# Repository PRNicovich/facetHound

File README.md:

# Facet Hound

Open hardware and software for the Facet Hound digital lapidary faceting machine.

Facet Hound is a mast-style faceting machine with digital readouts on all three axes, electronic indexing precise to less than 0.01 degrees, and a direct-driven lap powered by a brushless DC motor. It is designed to be replicated with readily available components and a minimum of custom parts. In 2025, the included components cost approximately $1,600.

Complete v7 and v8 assemblies are included as `Hardware/FacetHoundv7.step` and `Hardware/FacetHoundv8.step`. Subfolders of `Hardware/` contain vendor files for machining (`.step`, `.pdf`), 3D printing (`.stl`), PCB fabrication (`.brd`), and laser/plasma/waterjet cutting (`.dxf`). Commercially available parts are identified in the main design.

Subfolders of `Software/` contain the Arduino C++ sketches and desktop Python tools. The main module is a Raspberry Pi Pico 2, while peripheral controllers use RP2040 Zero boards.

## Current firmware

The current Pico 2 base plus RP2040 Zero mast, display, and keyboard-host
release is in
[`Software/FacetHound_SD_Loader`](Software/FacetHound_SD_Loader). It includes:

- Classic, Dynamic, and Static HX8357D display modes.
- A twist-wheel settings UI for machine and display configuration.
- Persistent CW/CCW indexing, Table Adapter, servo, calibration, and axis settings.
- Variable-length mark points with direct numeric editing.
- GemCad `.asc` and Facet Hound `.fct` loading from microSD.
- Source-validated `.fhc` geometry caching and a PC bulk converter.
- Runtime convex-gem mesh generation on the Pico 2 and streaming to the display.
- A documented USB CDC API and PC diagnostic/motion-test console.
- Matching streaming mast telemetry for tip, index, and force sensing.
- A dedicated PIO-USB keyboard host with the matching UART key protocol.

See the [release README](Software/FacetHound_SD_Loader/README.md) for SD wiring, dependencies, flashing instructions, limits, and verification results.

## Repository map

- `Hardware/`: complete assemblies and fabrication files.
- `Software/FacetHound_SD_Loader/`: current four-controller firmware release.
- `Software/caseModule/` and `displayModule/`: earlier module sketches.
- `Software/gemUtils/`: GemCad parsing, display prototypes, and geometry utilities.
- `Software/engraveUtils/`: engraving experiments.

These designs remain preliminary and may contain incomplete or untested elements. Contributions and bug fixes are welcome as pull requests.

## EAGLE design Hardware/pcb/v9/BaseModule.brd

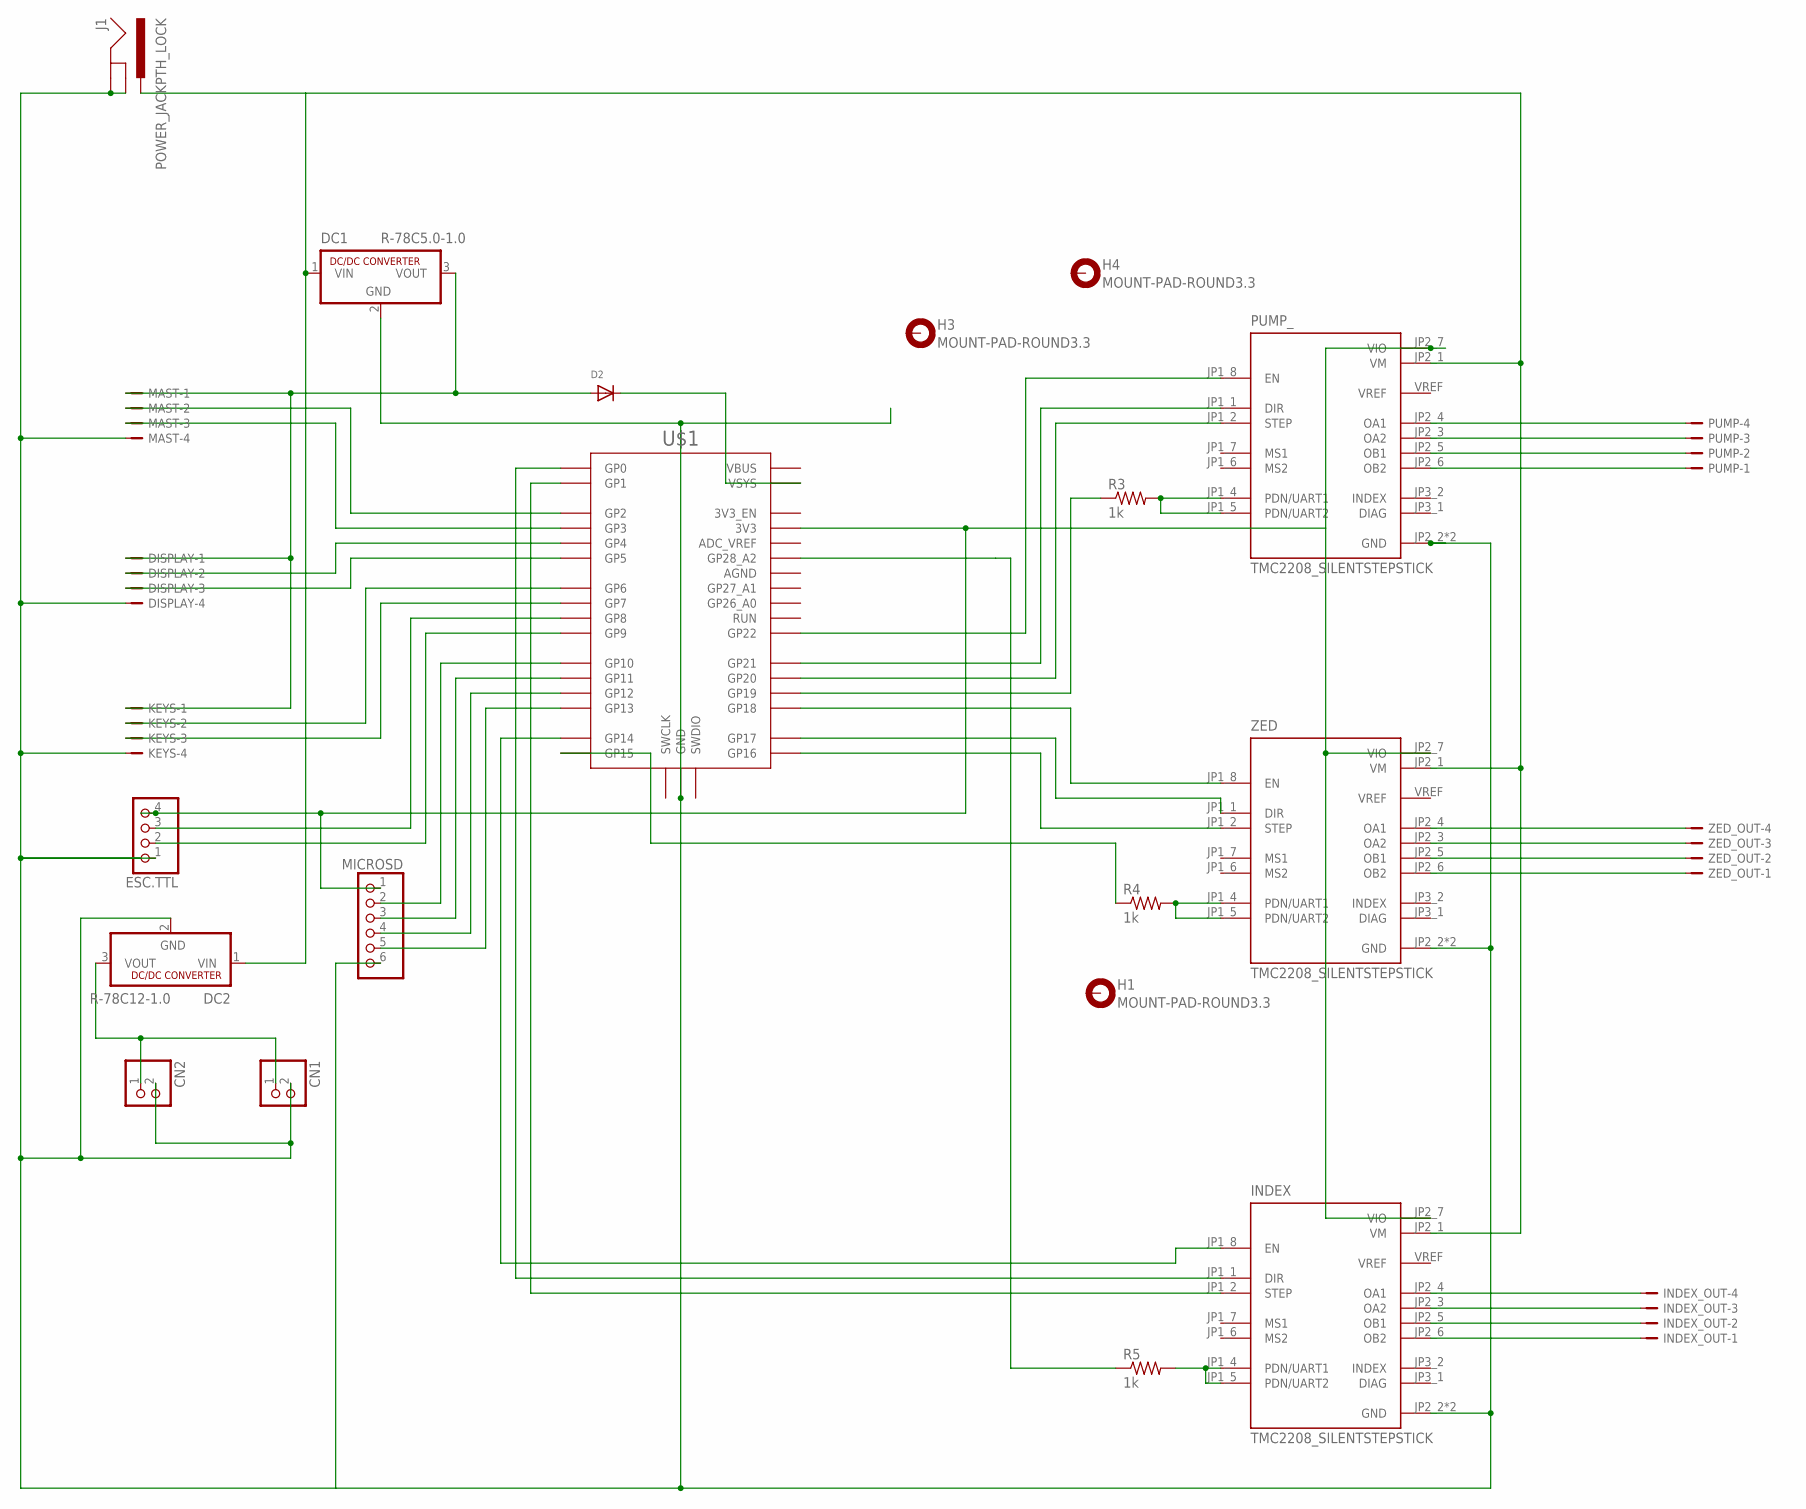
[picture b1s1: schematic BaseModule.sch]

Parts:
CN1, CN2: JST_2PIN-THM-RA; JST-PH-2-THM-RA
D2: DIODESMA; SMADIODE
DC1: R-78C5.0-1.0; SIP3
DC2: R-78C12-1.0; SIP3
DISPLAY: JST-PH-4_TH-V; B4B-PH-K-S
ESC.TTL: PINHD-1X4; 1X04
H1, H3, H4: MOUNT-PAD-ROUND3.3; 3,3-PAD
INDEX: TMC2208_SILENTSTEPSTICK; MODULE_TMC2208_SILENTSTEPSTICK
INDEX_OUT: JST-PH-4_TH-RA; S4B-PH-KL
J1: POWER_JACKPTH_LOCK; POWER_JACK_PTH_LOCK
KEYS: JST-PH-4_TH-V; B4B-PH-K-S
MAST: JST-PH-4_TH-V; B4B-PH-K-S
MICROSD: PINHD-1X6; 1X06
PUMP: JST-PH-4_TH-RA; S4B-PH-KL
PUMP_: TMC2208_SILENTSTEPSTICK; MODULE_TMC2208_SILENTSTEPSTICK
R3, R4, R5: 1k; R1206
U$1: RPI_PICO-TH; RPI_PICO_TH
ZED: TMC2208_SILENTSTEPSTICK; MODULE_TMC2208_SILENTSTEPSTICK
ZED_OUT: JST-PH-4_TH-RA; S4B-PH-KL

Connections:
5V: D2.C, U$1.VSYS
GND: CN1.2 (1), CN2.2 (1), DC1.2 (GND), DC2.2 (GND), DISPLAY.4, ESC.TTL.1, INDEX.JP2_2 (GND), INDEX.JP2_8 (GND), J1.GND, J1.GNDBREAK, KEYS.4, MAST.4, MICROSD.6, PUMP_.JP2_2 (GND), PUMP_.JP2_8 (GND), U$1.GND@1 (GND), U$1.GND@2 (GND), U$1.GND@3 (GND), U$1.GND@4 (GND), U$1.GND@5 (GND), U$1.GND@6 (GND), U$1.GND@7 (GND), U$1.GND@8 (GND), ZED.JP2_2 (GND), ZED.JP2_8 (GND)
KEYS: KEYS.2, U$1.GP6
unnamed: MICROSD.2, U$1.GP10
unnamed: MICROSD.3, U$1.GP11
unnamed: PUMP_.JP1_4 (PDN/UART1), PUMP_.JP1_5 (PDN/UART2), R3.2
unnamed: R4.2, ZED.JP1_4 (PDN/UART1), ZED.JP1_5 (PDN/UART2)
unnamed: DC1.1 (VIN), DC2.1 (VIN), INDEX.JP2_1 (VM), J1.PWR, PUMP_.JP2_1 (VM), ZED.JP2_1 (VM)
unnamed: U$1.GP18, ZED.JP1_8 (EN)
unnamed: INDEX.JP2_4 (OA1), INDEX_OUT.4
unnamed: MICROSD.4, U$1.GP12
unnamed: ESC.TTL.4, INDEX.JP2_7 (VIO), MICROSD.1, PUMP_.JP2_7 (VIO), U$1.3V3, ZED.JP2_7 (VIO)
unnamed: MICROSD.5, U$1.GP13
unnamed: R4.1, U$1.GP15
unnamed: D2.A, DC1.3 (VOUT), DISPLAY.1, KEYS.1, MAST.1
unnamed: INDEX.JP2_3 (OA2), INDEX_OUT.3
unnamed: ZED.JP2_4 (OA1), ZED_OUT.4
unnamed: ZED.JP2_3 (OA2), ZED_OUT.3
unnamed: ZED.JP2_5 (OB1), ZED_OUT.2
unnamed: ZED.JP2_6 (OB2), ZED_OUT.1
unnamed: PUMP.4, PUMP_.JP2_4 (OA1)
unnamed: PUMP.3, PUMP_.JP2_3 (OA2)
unnamed: PUMP.2, PUMP_.JP2_5 (OB1)
unnamed: PUMP.1, PUMP_.JP2_6 (OB2)
unnamed: U$1.GP17, ZED.JP1_1 (DIR)
unnamed: U$1.GP16, ZED.JP1_2 (STEP)
unnamed: PUMP_.JP1_8 (EN), U$1.GP22
unnamed: PUMP_.JP1_1 (DIR), U$1.GP21
unnamed: PUMP_.JP1_2 (STEP), U$1.GP20
unnamed: R3.1, U$1.GP19
unnamed: MAST.2, U$1.GP2
unnamed: MAST.3, U$1.GP3
unnamed: DISPLAY.2, U$1.GP4
unnamed: DISPLAY.3, U$1.GP5
unnamed: KEYS.3, U$1.GP7
unnamed: ESC.TTL.3, U$1.GP8
unnamed: INDEX.JP2_5 (OB1), INDEX_OUT.2
unnamed: ESC.TTL.2, U$1.GP9
unnamed: CN1.1 (2), CN2.1 (2), DC2.3 (VOUT)
unnamed: INDEX.JP2_6 (OB2), INDEX_OUT.1
unnamed: INDEX.JP1_8 (EN), U$1.GP14
unnamed: R5.1, U$1.GP28_A2
unnamed: INDEX.JP1_4 (PDN/UART1), INDEX.JP1_5 (PDN/UART2), R5.2
unnamed: INDEX.JP1_1 (DIR), U$1.GP0
unnamed: INDEX.JP1_2 (STEP), U$1.GP1

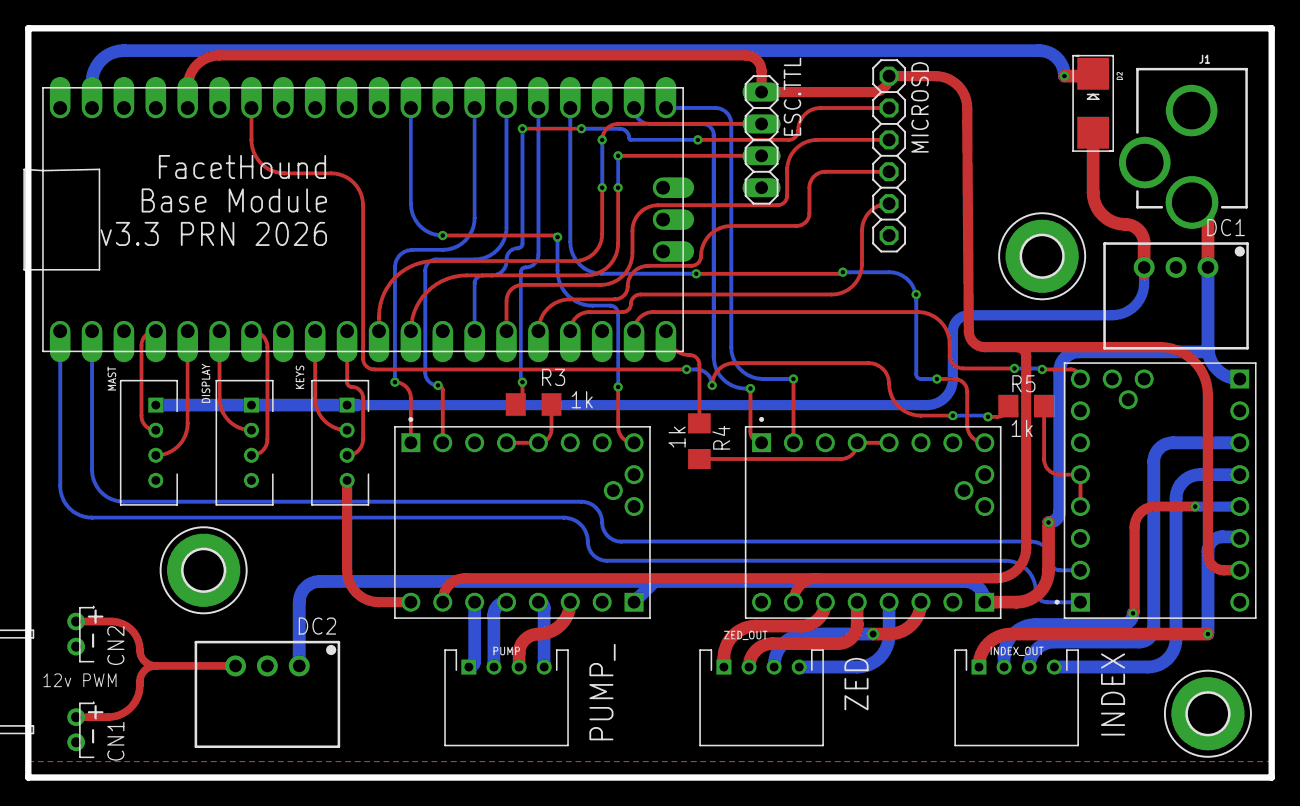
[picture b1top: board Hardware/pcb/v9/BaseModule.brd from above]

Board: 2 copper layers, 99.1 x 59.7 mm, 24 parts (0 on the bottom side), 45 nets.

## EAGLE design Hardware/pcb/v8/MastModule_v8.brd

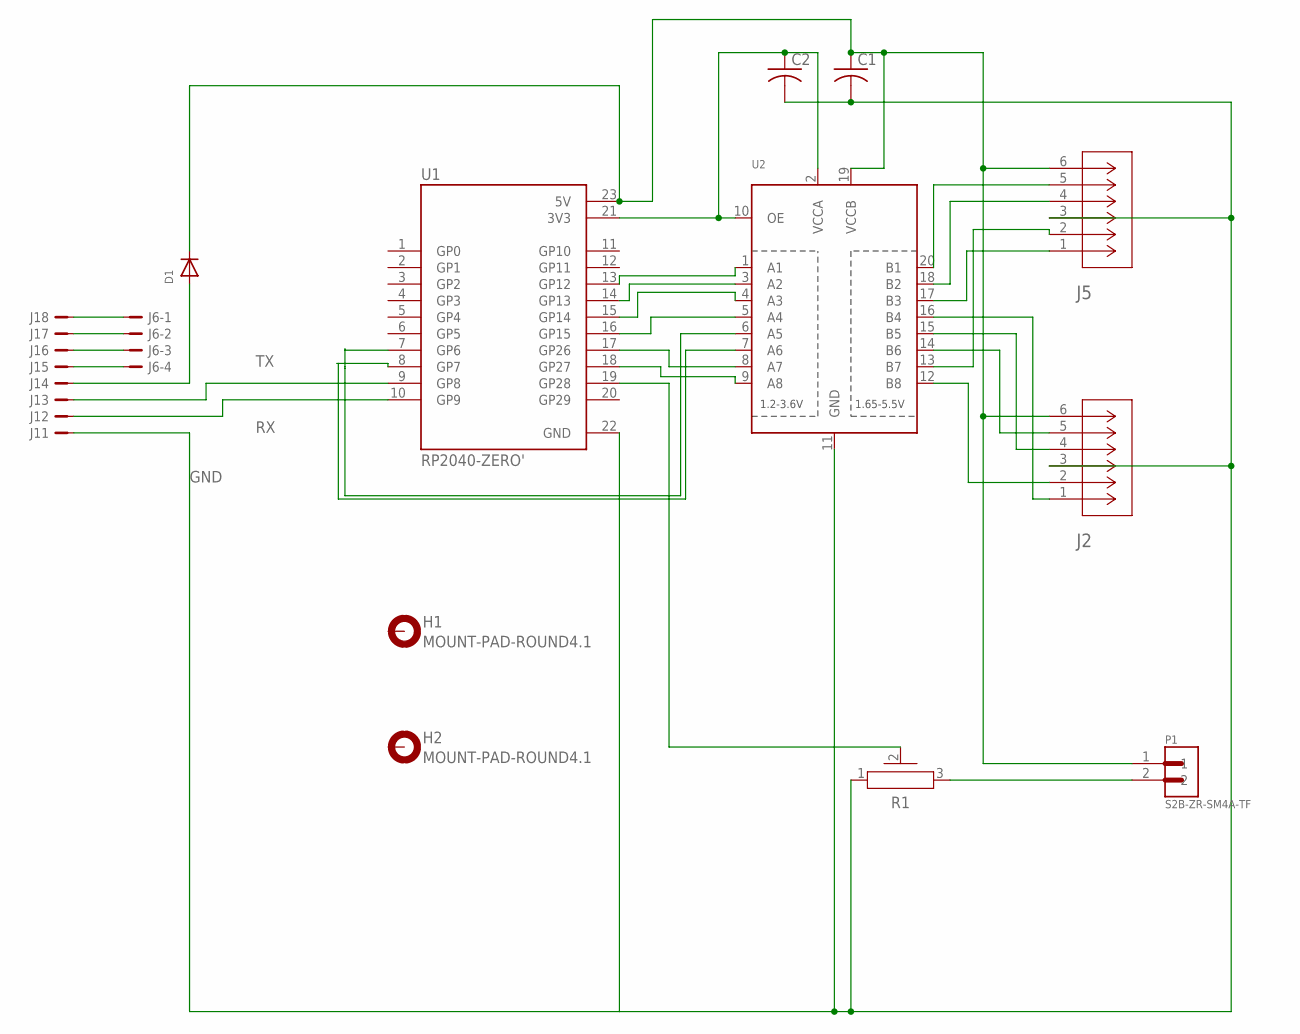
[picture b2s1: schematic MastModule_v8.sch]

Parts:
C1, C2: C-USC1210; C1210
D1: DIODESMA; SMADIODE
H1, H2: MOUNT-PAD-ROUND4.1; 4,1-PAD
J1: B8B-PH-K-S
J2, J5: 2132260630CONN_2132260000-SD_06_MOL; CONN_2132260000-SD_06_MOL
J6: JST-PH-4_TH-RA; S4B-PH-KL
P1: S2B-ZR-SM4A-TF; JST_S2B-ZR-SM4A-TF
R1: PV36X
U1: RP2040-ZERO'; MODULE_RP2040-ZERO
U2: TXB0108PWR; TSSOP20

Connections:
3V3: C2.1, U1.21 (3V3), U2.2 (VCCA), U2.10 (OE)
5V: C1.1, D1.C, J2.6, J5.6, P1.1, U1.23 (5V), U2.19 (VCCB)
GND: C1.2, C2.2, J1.1, J2.3, J5.3, R1.1, U1.22 (GND), U2.11 (GND)
unnamed: J1.8, J6.1
unnamed: J1.7, J6.2
unnamed: J1.6, J6.3
unnamed: J1.5, J6.4
unnamed: D1.A, J1.4
unnamed: U1.17 (GP26), U2.8 (A7)
unnamed: J5.5, U2.20 (B1)
unnamed: J5.4, U2.18 (B2)
unnamed: R1.2, U1.19 (GP28)
unnamed: P1.2, R1.3
unnamed: J5.1, U2.17 (B3)
unnamed: J2.1, U2.16 (B4)
unnamed: J2.4, U2.15 (B5)
unnamed: J2.5, U2.14 (B6)
unnamed: U1.18 (GP27), U2.9 (A8)
unnamed: J5.2, U2.13 (B7)
unnamed: J2.2, U2.12 (B8)
unnamed: U1.8 (GP7), U2.7 (A6)
unnamed: U1.7 (GP6), U2.6 (A5)
unnamed: U1.13 (GP12), U2.1 (A1)
unnamed: U1.14 (GP13), U2.3 (A2)
unnamed: U1.15 (GP14), U2.4 (A3)
unnamed: U1.16 (GP15), U2.5 (A4)
RX: J1.2, U1.10 (GP9)
TX: J1.3, U1.9 (GP8)

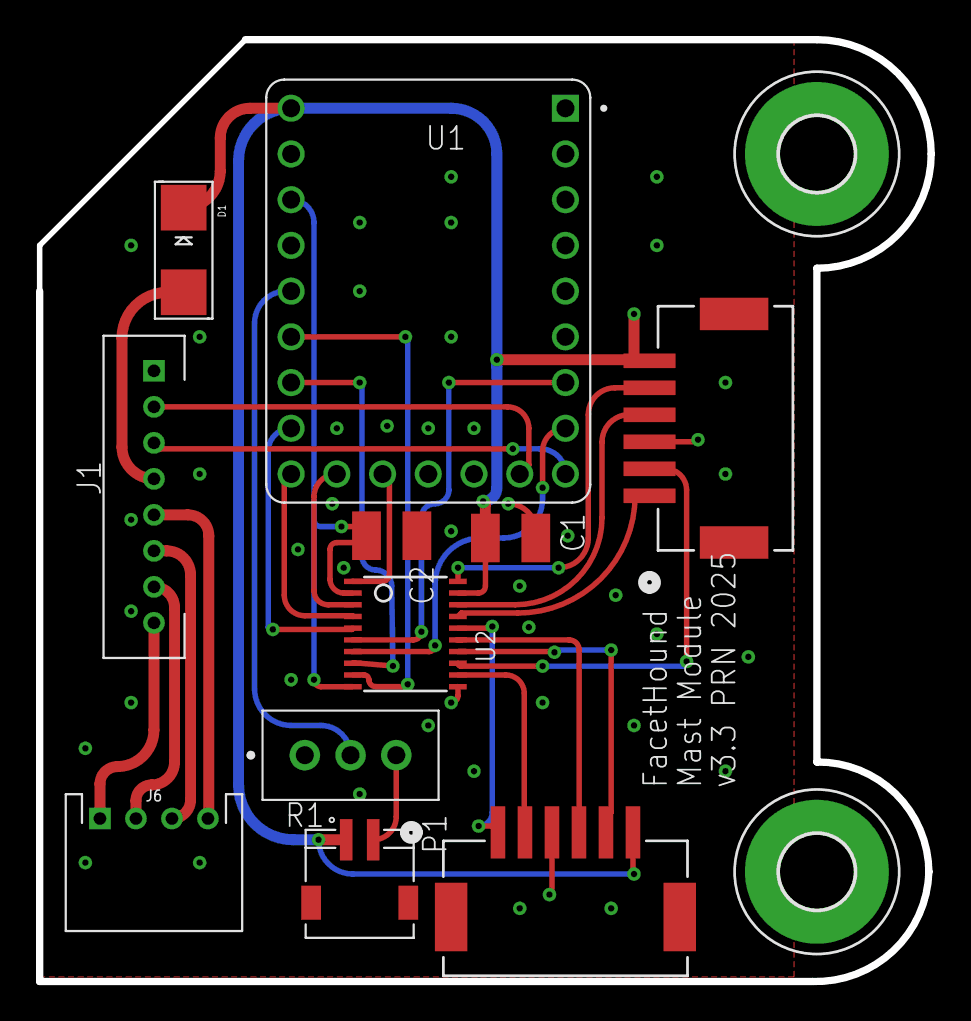
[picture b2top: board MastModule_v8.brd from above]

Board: 2 copper layers, 49.5 x 52.3 mm, 13 parts (0 on the bottom side), 28 nets.

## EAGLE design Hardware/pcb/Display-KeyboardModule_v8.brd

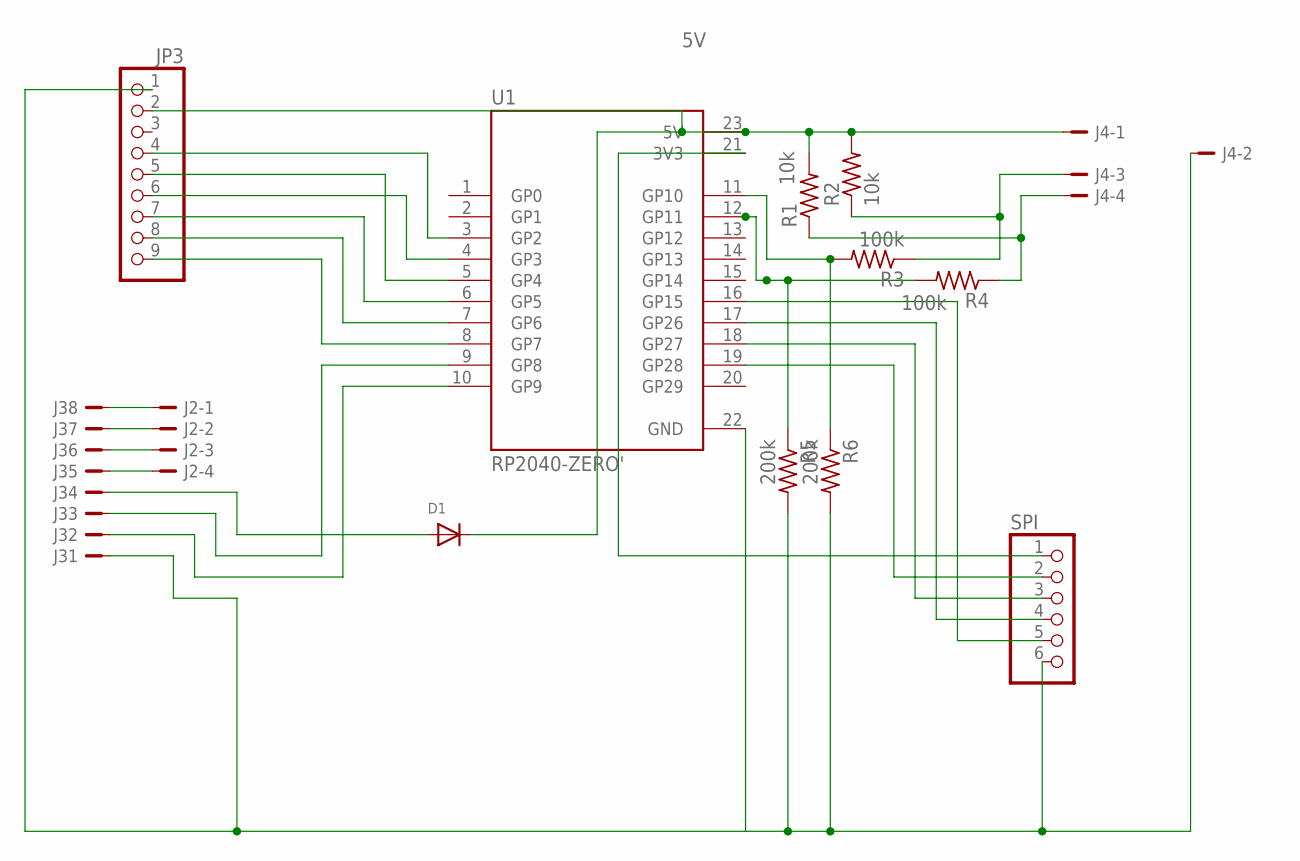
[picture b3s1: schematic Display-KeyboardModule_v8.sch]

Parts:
D1: DIODESMA; SMADIODE
J2, J4: JST-PH-4_TH-RA; S4B-PH-KL
J3: B8B-PH-K-S
JP3: PINHD-1X9; 1X09-BIG
R1, R2: 10k; R1206
R3, R4: 100k; R1206
R5, R6: 200k; R1206
SPI: PINHD-1X6; 1X06
U1: RP2040-ZERO'; MODULE_RP2040-ZERO

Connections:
5V: D1.C, J4.1, JP3.2, R1.2, R2.2, U1.23 (5V)
GND: J3.1, J4.2, JP3.1, R5.2, R6.2, SPI.6, U1.22 (GND)
unnamed: D1.A, J3.4
unnamed: J2.1, J3.8
unnamed: JP3.4, U1.3 (GP2)
unnamed: J3.3, U1.9 (GP8)
unnamed: J3.2, U1.10 (GP9)
unnamed: JP3.6, U1.4 (GP3)
unnamed: JP3.5, U1.5 (GP4)
unnamed: JP3.7, U1.6 (GP5)
unnamed: JP3.8, U1.7 (GP6)
unnamed: JP3.9, U1.8 (GP7)
unnamed: SPI.2, U1.19 (GP28)
unnamed: J4.3, R2.1, R3.1
unnamed: J2.2, J3.7
unnamed: J2.3, J3.6
unnamed: J2.4, J3.5
unnamed: SPI.3, U1.18 (GP27)
unnamed: J4.4, R1.1, R4.1
unnamed: SPI.4, U1.17 (GP26)
unnamed: R3.2, R6.1, U1.11 (GP10)
unnamed: SPI.5, U1.16 (GP15)
unnamed: SPI.1, U1.21 (3V3)
unnamed: R4.2, R5.1, U1.12 (GP11)

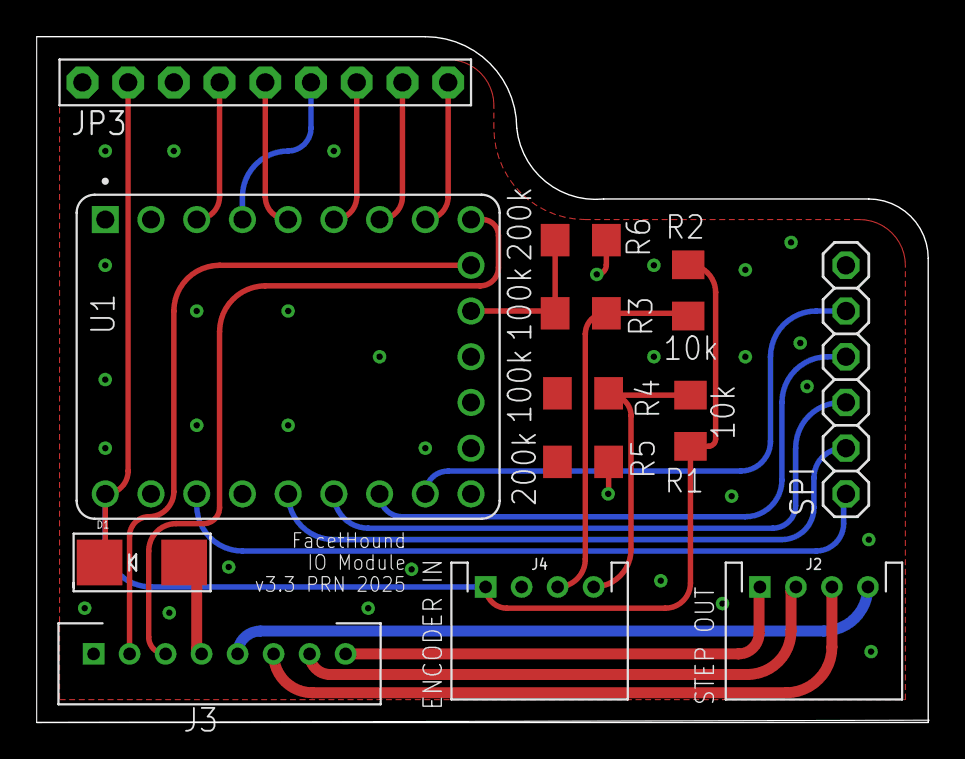
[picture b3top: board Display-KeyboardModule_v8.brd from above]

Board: 2 copper layers, 49.5 x 38.1 mm, 13 parts (0 on the bottom side), 24 nets.

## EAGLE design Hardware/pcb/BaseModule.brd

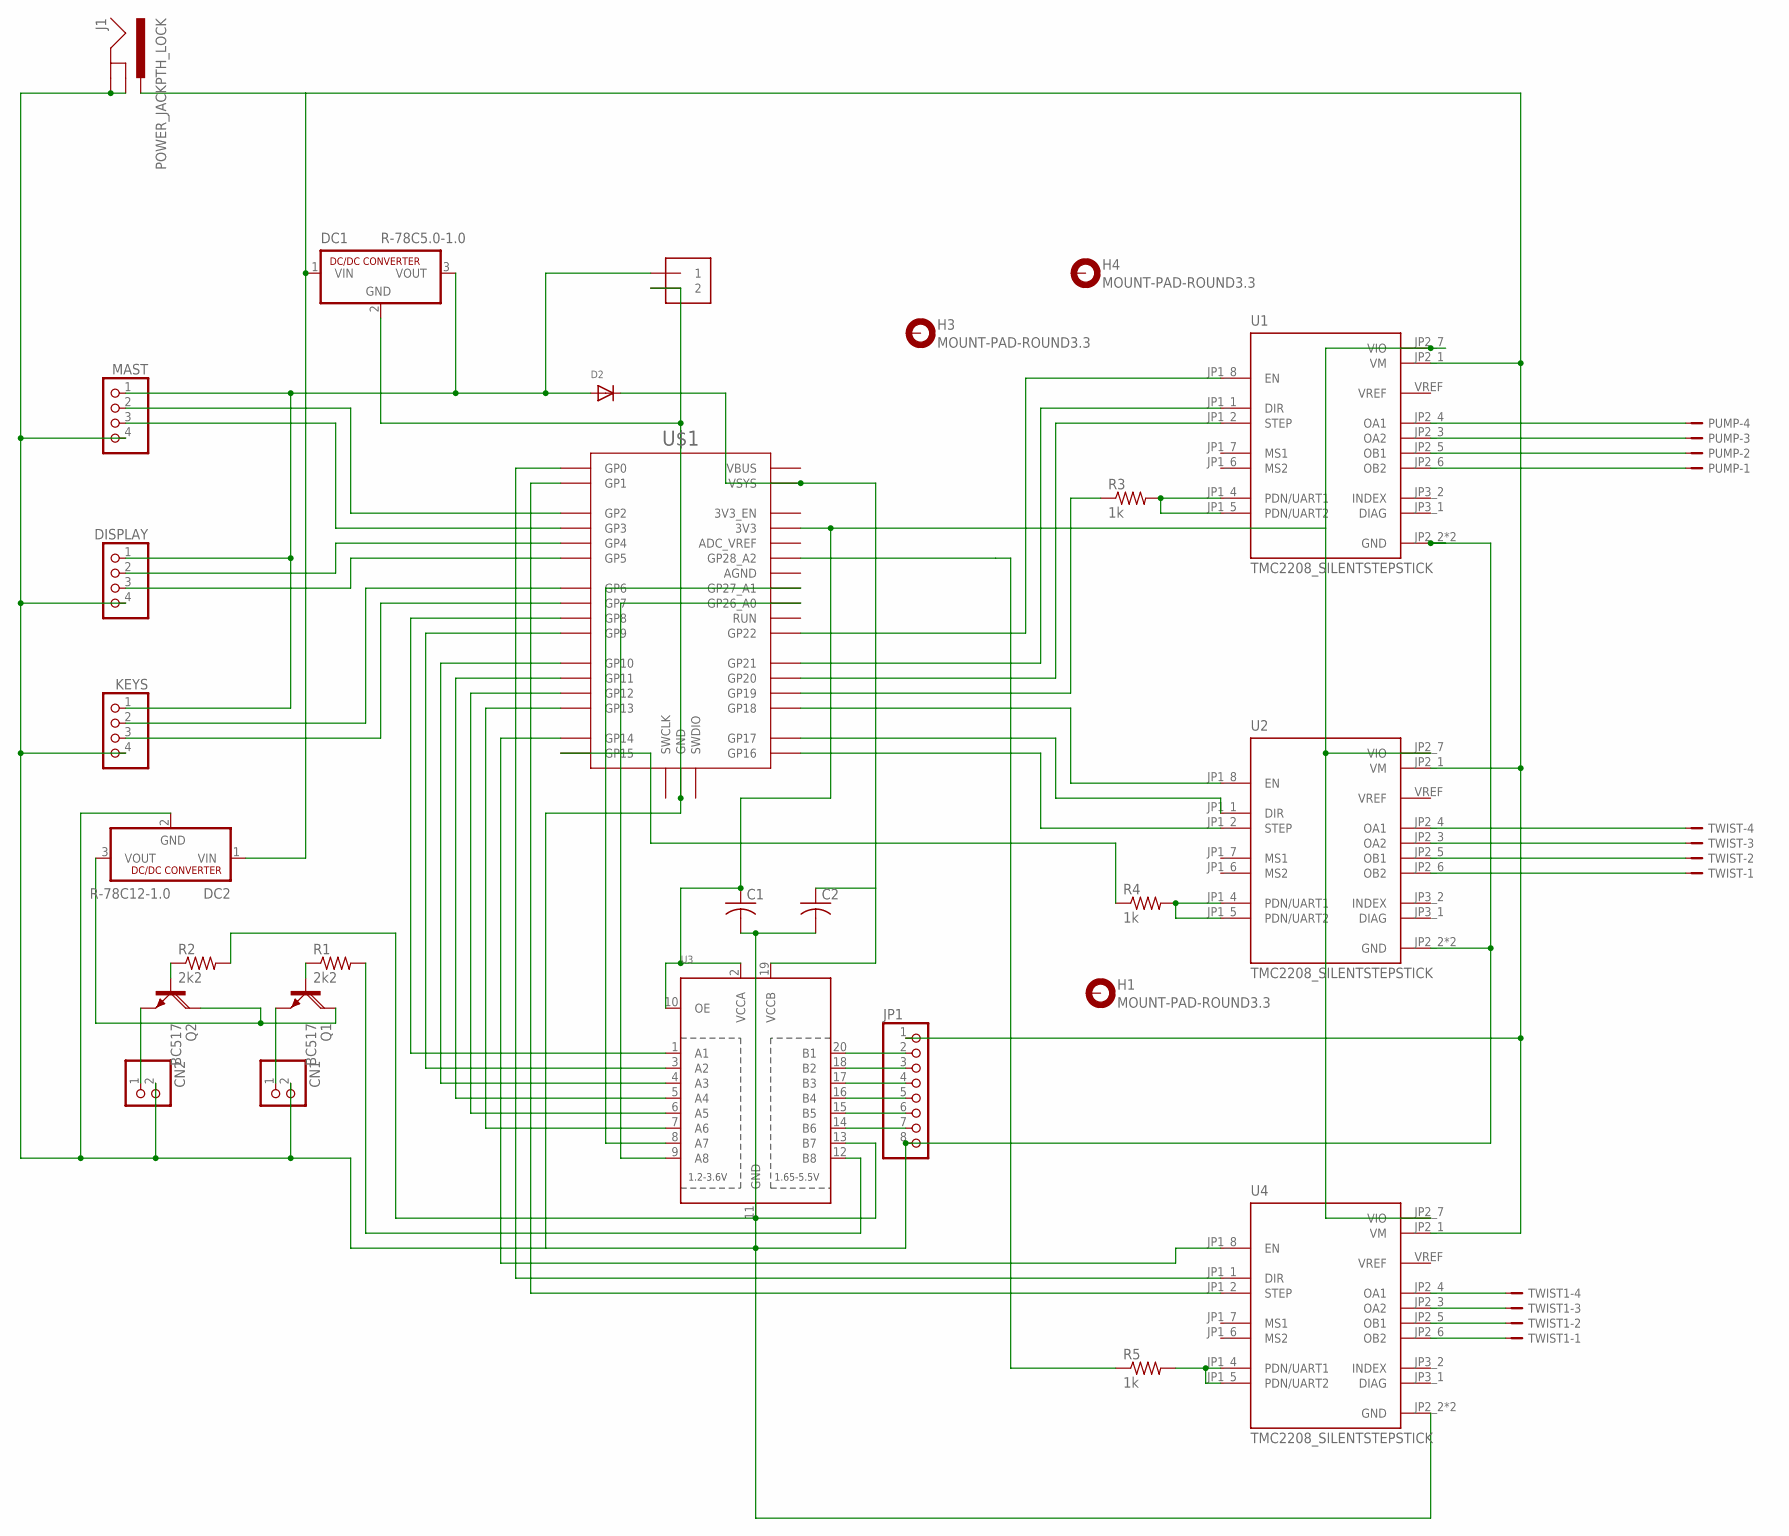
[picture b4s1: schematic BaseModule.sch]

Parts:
C1, C2: C-USC1206; C1206
CN1, CN2: JST_2PIN-THM-RA; JST-PH-2-THM-RA
D2: DIODESMA; SMADIODE
DC1: R-78C5.0-1.0; SIP3
DC2: R-78C12-1.0; SIP3
DISPLAY: PINHD-1X4; 1X04
H1, H3, H4: MOUNT-PAD-ROUND3.3; 3,3-PAD
J1: POWER_JACKPTH_LOCK; POWER_JACK_PTH_LOCK
J2: 1X2-3.5MM
JP1: PINHD-1X8-3.5MM; 1X08-3.5MM
KEYS: PINHD-1X4; 1X04
MAST: PINHD-1X4; 1X04
PUMP: JST-PH-4_TH-RA; S4B-PH-KL
Q1, Q2: BC517; SOT54A
R1, R2: 2k2; R1206
R3, R4, R5: 1k; R1206
TWIST, TWIST1: JST-PH-4_TH-RA; S4B-PH-KL
U1, U2, U4: TMC2208_SILENTSTEPSTICK; MODULE_TMC2208_SILENTSTEPSTICK
U3: TXB0108PWR; TSSOP20
U$1: RPI_PICO-TH; RPI_PICO_TH

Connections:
GND: C1.2, C2.2, CN1.2 (1), CN2.2 (1), DC1.2 (GND), DC2.2 (GND), DISPLAY.4, J1.GND, J1.GNDBREAK, J2.2, JP1.8, KEYS.4, MAST.4, U1.JP2_2 (GND), U1.JP2_8 (GND), U2.JP2_2 (GND), U2.JP2_8 (GND), U3.11 (GND), U4.JP2_2 (GND), U4.JP2_8 (GND), U$1.GND@1 (GND), U$1.GND@2 (GND), U$1.GND@3 (GND), U$1.GND@4 (GND), U$1.GND@5 (GND), U$1.GND@6 (GND), U$1.GND@7 (GND), U$1.GND@8 (GND)
unnamed: Q1.B, R1.1
unnamed: Q2.B, R2.1
unnamed: R3.2, U1.JP1_4 (PDN/UART1), U1.JP1_5 (PDN/UART2)
unnamed: R4.2, U2.JP1_4 (PDN/UART1), U2.JP1_5 (PDN/UART2)
unnamed: DC1.1 (VIN), DC2.1 (VIN), J1.PWR, JP1.1, U1.JP2_1 (VM), U2.JP2_1 (VM), U4.JP2_1 (VM)
unnamed: U2.JP1_8 (EN), U$1.GP18
unnamed: TWIST1.4, U4.JP2_4 (OA1)
unnamed: C2.1, D2.C, U3.19 (VCCB), U$1.VSYS
unnamed: U3.7 (A6), U$1.GP13
unnamed: CN2.1 (2), Q2.E
unnamed: JP1.2, U3.20 (B1)
unnamed: R4.1, U$1.GP15
unnamed: D2.A, DC1.3 (VOUT), DISPLAY.1, J2.1, KEYS.1, MAST.1
unnamed: TWIST1.3, U4.JP2_3 (OA2)
unnamed: TWIST.4, U2.JP2_4 (OA1)
unnamed: TWIST.3, U2.JP2_3 (OA2)
unnamed: TWIST.2, U2.JP2_5 (OB1)
unnamed: TWIST.1, U2.JP2_6 (OB2)
unnamed: PUMP.4, U1.JP2_4 (OA1)
unnamed: PUMP.3, U1.JP2_3 (OA2)
unnamed: PUMP.2, U1.JP2_5 (OB1)
unnamed: PUMP.1, U1.JP2_6 (OB2)
unnamed: U2.JP1_1 (DIR), U$1.GP17
unnamed: U2.JP1_2 (STEP), U$1.GP16
unnamed: JP1.3, U3.18 (B2)
unnamed: U1.JP1_8 (EN), U$1.GP22
unnamed: U1.JP1_1 (DIR), U$1.GP21
unnamed: U1.JP1_2 (STEP), U$1.GP20
unnamed: R3.1, U$1.GP19
unnamed: MAST.2, U$1.GP2
unnamed: MAST.3, U$1.GP3
unnamed: DISPLAY.2, U$1.GP4
unnamed: DISPLAY.3, U$1.GP5
unnamed: KEYS.2, U$1.GP6
unnamed: KEYS.3, U$1.GP7
unnamed: CN1.1 (2), Q1.E
unnamed: JP1.4, U3.17 (B3)
unnamed: JP1.5, U3.16 (B4)
unnamed: JP1.6, U3.15 (B5)
unnamed: JP1.7, U3.14 (B6)
unnamed: U3.1 (A1), U$1.GP8
unnamed: TWIST1.2, U4.JP2_5 (OB1)
unnamed: C1.1, U1.JP2_7 (VIO), U2.JP2_7 (VIO), U3.2 (VCCA), U3.10 (OE), U4.JP2_7 (VIO), U$1.3V3
unnamed: R2.2, U3.13 (B7)
unnamed: R1.2, U3.12 (B8)
unnamed: U3.3 (A2), U$1.GP9
unnamed: U3.4 (A3), U$1.GP10
unnamed: U3.5 (A4), U$1.GP11
unnamed: U3.6 (A5), U$1.GP12
unnamed: DC2.3 (VOUT), Q1.C, Q2.C
unnamed: U3.8 (A7), U$1.GP27_A1
unnamed: U3.9 (A8), U$1.GP26_A0
unnamed: TWIST1.1, U4.JP2_6 (OB2)
unnamed: U4.JP1_8 (EN), U$1.GP14
unnamed: R5.1, U$1.GP28_A2
unnamed: R5.2, U4.JP1_4 (PDN/UART1), U4.JP1_5 (PDN/UART2)
unnamed: U4.JP1_1 (DIR), U$1.GP0
unnamed: U4.JP1_2 (STEP), U$1.GP1

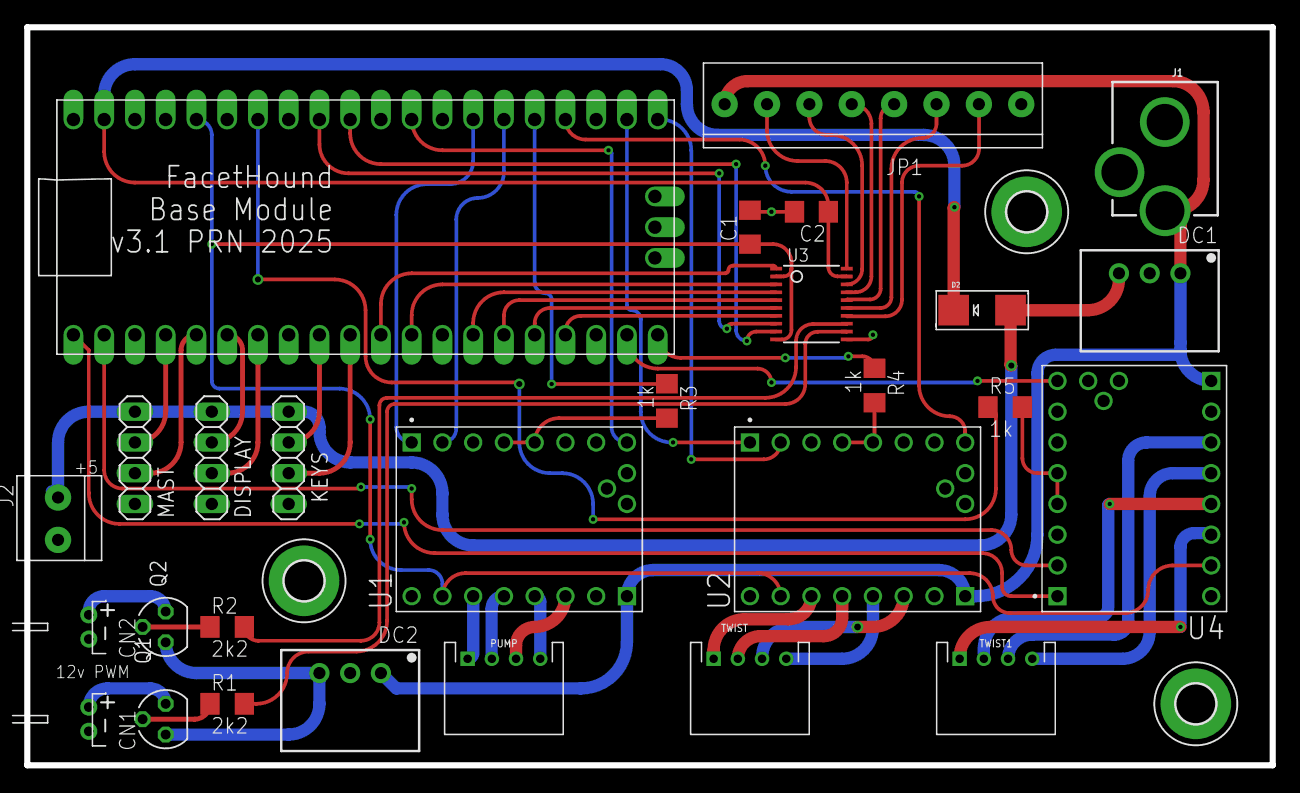
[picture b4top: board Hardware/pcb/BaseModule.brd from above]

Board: 2 copper layers, 102.9 x 61.0 mm, 31 parts (0 on the bottom side), 59 nets.

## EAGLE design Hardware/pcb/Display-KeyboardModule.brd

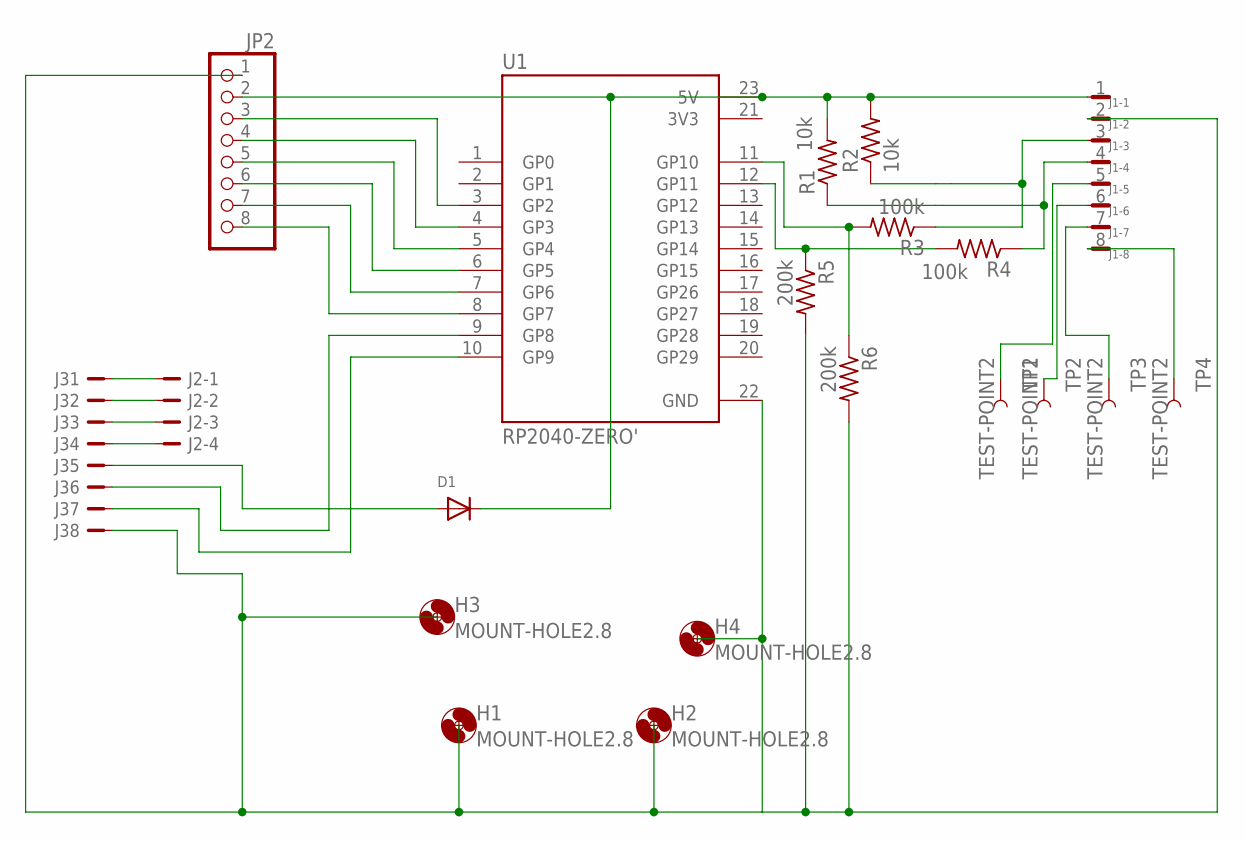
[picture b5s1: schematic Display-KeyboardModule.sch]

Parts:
D1: DIODESMA; SMADIODE
H1, H2, H3, H4: MOUNT-HOLE2.8; 2,8
J1: JST-SH-8_RA; SM08B-SRSS-TB
J2: JST-PH-4_TH-RA; S4B-PH-KL
J3: B8B-PH-K-S
JP2: PINHD-1X8/90; 1X08/90
R1, R2: 10k; R1206
R3, R4: 100k; R1206
R5, R6: 200k; R1206
TP1, TP2, TP3, TP4: TEST-POINT2; PAD.02X.02
U1: RP2040-ZERO'; MODULE_RP2040-ZERO

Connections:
3V3: U1.21 (3V3)
GND: J1.2, J3.8, JP2.1, R5.2, R6.2, U1.22 (GND)
unnamed: D1.A, J3.5
unnamed: J2.1, J3.1
unnamed: JP2.3, U1.3 (GP2)
unnamed: J3.6, U1.9 (GP8)
unnamed: J3.7, U1.10 (GP9)
unnamed: JP2.4, U1.4 (GP3)
unnamed: JP2.5, U1.5 (GP4)
unnamed: JP2.6, U1.6 (GP5)
unnamed: JP2.7, U1.7 (GP6)
unnamed: JP2.8, U1.8 (GP7)
unnamed: D1.C, J1.1, JP2.2, R1.2, R2.2, U1.23 (5V)
unnamed: J1.3, R2.1, R3.1
unnamed: J2.2, J3.2
unnamed: J1.8, TP4.1
unnamed: J1.7, TP3.1
unnamed: J1.6, TP2.1
unnamed: J1.4, R1.1, R4.1
unnamed: J1.5, TP1.1
unnamed: R4.2, R5.1, U1.12 (GP11)
unnamed: R3.2, R6.1, U1.11 (GP10)
unnamed: J2.3, J3.3
unnamed: J2.4, J3.4

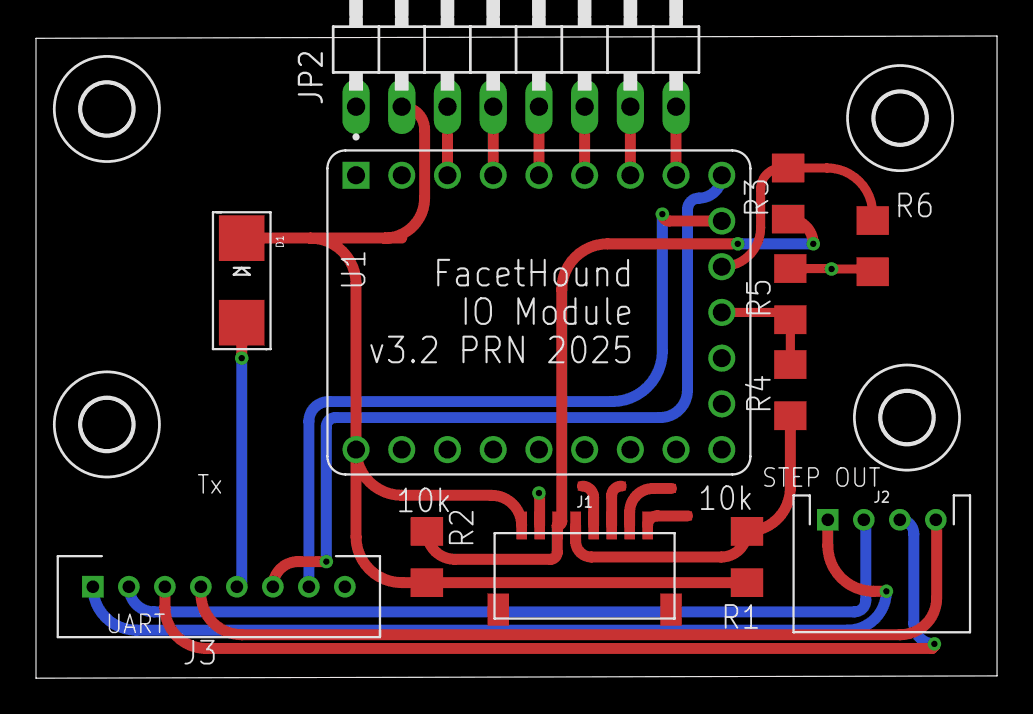
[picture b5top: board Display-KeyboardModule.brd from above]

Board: 2 copper layers, 53.4 x 35.7 mm, 20 parts (0 on the bottom side), 23 nets.

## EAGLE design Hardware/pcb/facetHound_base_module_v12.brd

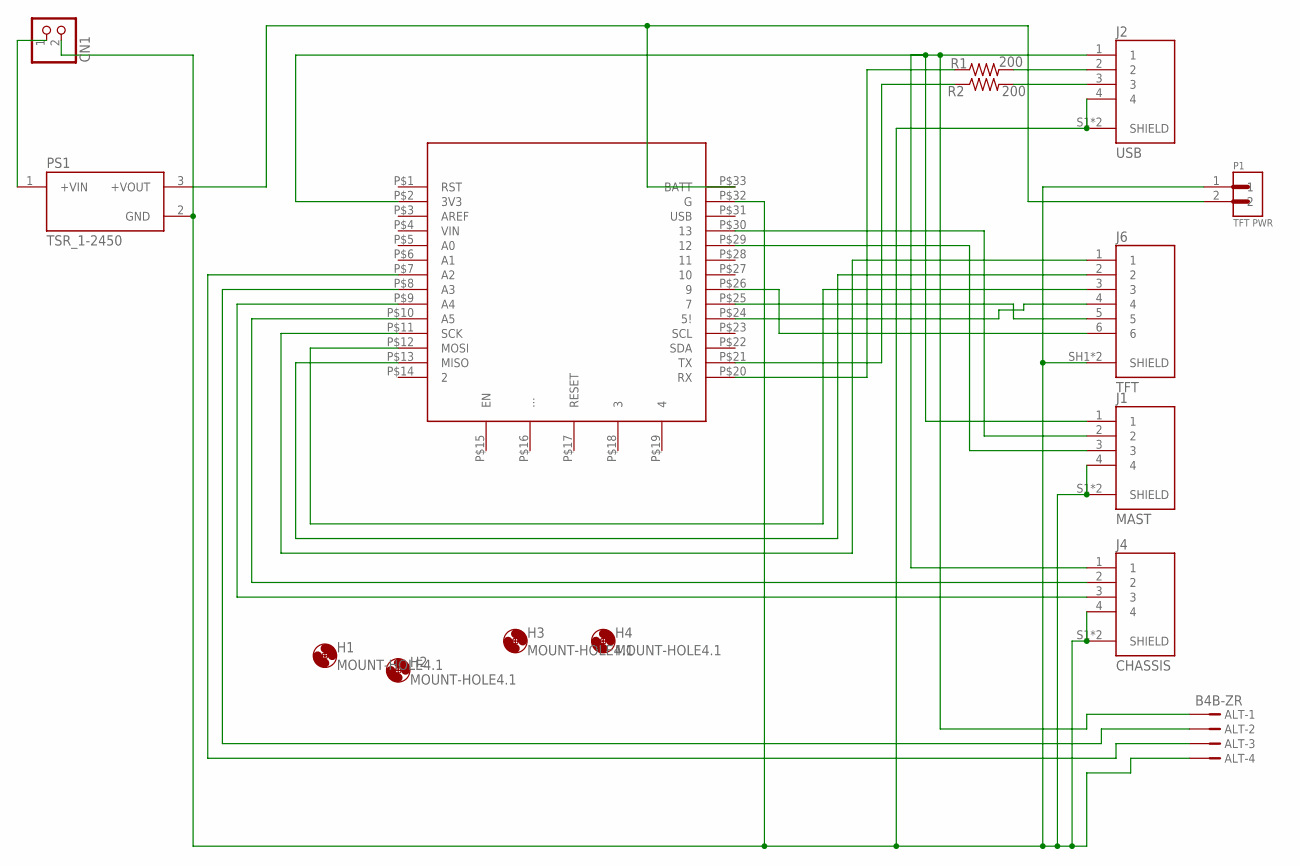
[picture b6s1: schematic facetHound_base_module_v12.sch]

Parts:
ALT: B4B-ZR
CN1: JST_2PIN-THM-RA; JST-PH-2-THM-RA
H1, H2, H3, H4: MOUNT-HOLE4.1; 4,1
J1: MAST; JST_S4B-ZR-SM4A-TF(LF)(SN)
J2: USB; JST_S4B-ZR-SM4A-TF(LF)(SN)
J4: CHASSIS; JST_S4B-ZR-SM4A-TF(LF)(SN)
J6: TFT; JST_S6B-ZR-SM4A-TF(LF)(SN)
P1: TFT PWR; JST_S2B-ZR-SM4A-TF
PS1: TSR_1-2450; CONV_TSR_1-2450
R1, R2: 200; M1206
U$1: ITSYBITSY_M4

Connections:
GND: ALT.4, CN1.2 (1), J1.4, J1.S1 (SHIELD), J1.S2 (SHIELD), J2.4, J2.S1 (SHIELD), J2.S2 (SHIELD), J4.4, J4.S1 (SHIELD), J4.S2 (SHIELD), J6.SH1 (SHIELD), J6.SH2 (SHIELD), P1.1, PS1.2 (GND), U$1.P$32 (G)
unnamed: CN1.1 (2), PS1.1 (+VIN)
unnamed: P1.2, PS1.3 (+VOUT), U$1.P$33 (BATT)
unnamed: R2.1, U$1.P$21 (TX)
unnamed: ALT.3, U$1.P$7 (A2)
unnamed: J6.1, U$1.P$11 (SCK)
unnamed: ALT.1, J1.1, J2.1, J4.1, U$1.P$2 (3V3)
unnamed: J6.2, U$1.P$13 (MISO)
unnamed: J2.2, R1.2
unnamed: R1.1, U$1.P$20 (RX)
unnamed: J6.3, U$1.P$12 (MOSI)
unnamed: J6.5, U$1.P$25 (7)
unnamed: J6.4, U$1.P$24 (5!)
unnamed: J6.6, U$1.P$26 (9)
unnamed: J1.2, U$1.P$30 (13)
unnamed: J1.3, U$1.P$29 (12)
unnamed: J4.2, U$1.P$10 (A5)
unnamed: J4.3, U$1.P$9 (A4)
unnamed: J2.3, R2.2
unnamed: ALT.2, U$1.P$8 (A3)

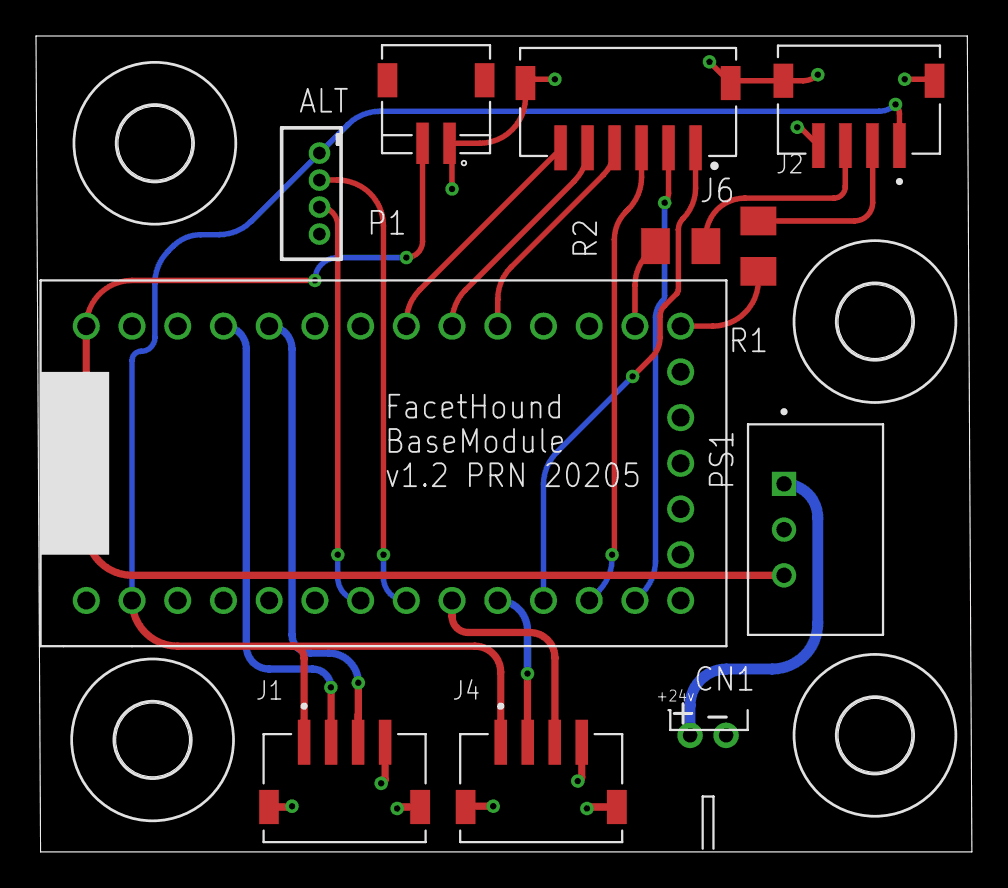
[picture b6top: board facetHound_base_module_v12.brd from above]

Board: 2 copper layers, 52.0 x 45.3 mm, 15 parts (0 on the bottom side), 20 nets.

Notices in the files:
parts and their libraries:
SparkFun-Connectors: Licensing: Creative Commons ShareAlike 4.0 International - https://creativecommons.org/licenses/by-sa/4.0
COPYRIGHT: Copyright (C) 2025 Ultra Librarian. All rights reserved.
